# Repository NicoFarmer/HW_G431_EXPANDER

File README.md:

# HW_G431_EXPANDER
Carte électronique d'exention pour CPU STM32 G431KB

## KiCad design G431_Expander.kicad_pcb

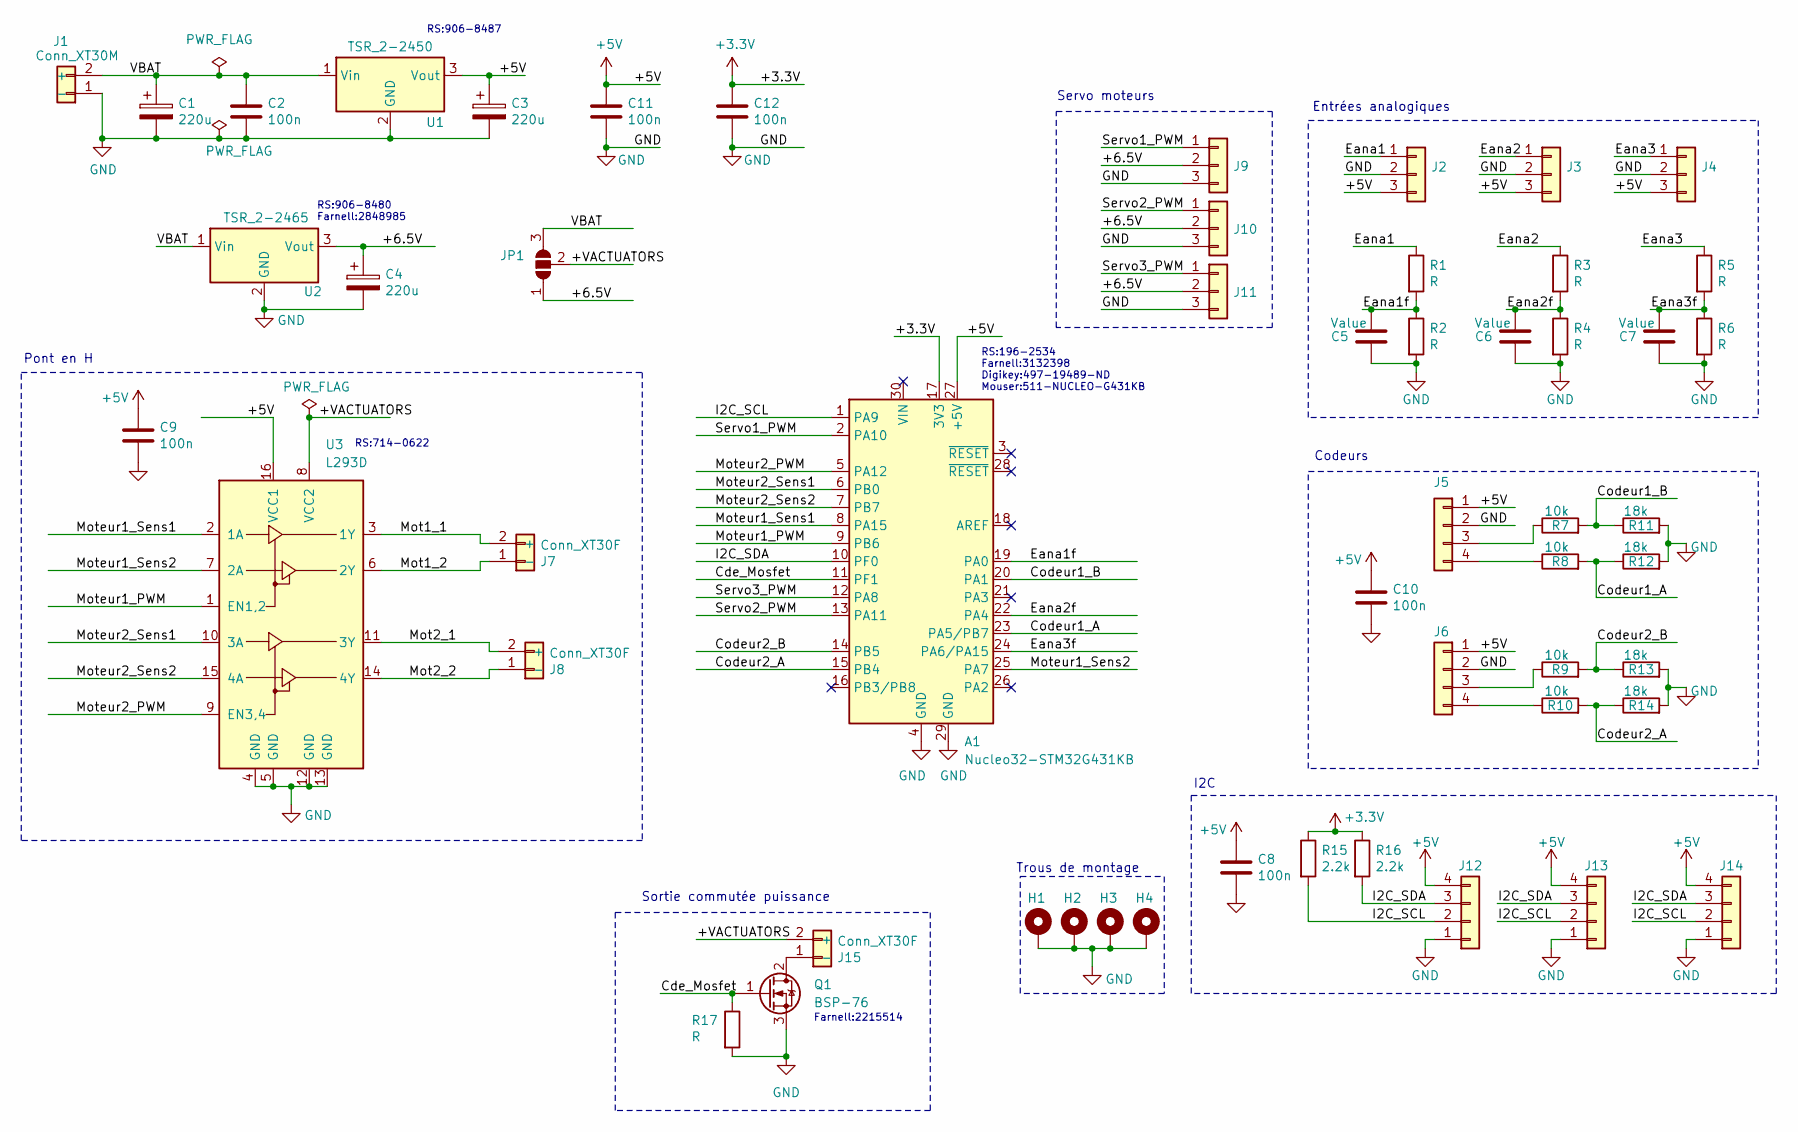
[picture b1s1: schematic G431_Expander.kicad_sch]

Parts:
A1: Nucleo32-STM32G431KB; Nucleo32-STM32-2x15pins
C1, C3, C4: 220u; C_Radial_D8.0mm_H11.5mm_P3.50mm
C2, C8, C9, C10, C11, C12: 100n; C_1206_3216Metric
C5, C6, C7: Value; C_1206_3216Metric
H1, H2, H3, H4: MountingHole_Pad; MountingHole_3.2mm_M3_Pad
J1: Conn_XT30M; AMASS_XT30UPB-M_1x02_P5.0mm_Vertical
J2, J3, J4: Conn_01x03; Molex_KK-254_AE-6410-03A_1x03_P2.54mm_Vertical
J5, J6, J12, J13, J14: Conn_01x04; Molex_KK-254_AE-6410-04A_1x04_P2.54mm_Vertical
J7, J8, J15: Conn_XT30F; AMASS_XT30UPB-F_1x02_P5.0mm_Vertical
J9, J10, J11: Conn_01x03; Servomotor-3x254
JP1: SolderJumper_3_Open; PinHeader_1x03_P2.54mm_Vertical
Q1: BSP-76; SOT-223-3_TabPin2
R1, R2, R3, R4, R5, R6, R17: R; R_1206_3216Metric
R7, R8, R9, R10: 10k; R_1206_3216Metric
R11, R12, R13, R14: 18k; R_1206_3216Metric
R15, R16: 2.2k; R_1206_3216Metric
U1: TSR_2-2450; Converter_DCDC_TRACO_TSR-1_THT
U2: TSR_2-2465; Converter_DCDC_TRACO_TSR-1_THT
U3: L293D; DIP-16_W7.62mm

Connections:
+3.3V: A1.17 (3V3), C12.1, R15.1, R16.1
+5V: A1.27 (+5V), C3.1, C8.1, C9.1, C10.1, C11.1, J2.3, J3.3, J4.3, J5.1, J6.1, J12.4, J13.4, J14.4, U1.3 (Vout), U3.16 (VCC1)
/+6.5V: C4.1, J9.2, J10.2, J11.2, JP1.1 (A), U2.3 (Vout)
/+VACTUATORS: J15.2 (+), JP1.2 (C), U3.8 (VCC2)
/Cde_Mosfet: A1.11 (PF1), Q1.1 (G), R17.1
/Codeur1_A: A1.23 (PA5/PB7), R8.2, R12.1
/Codeur1_B: A1.20 (PA1), R7.2, R11.1
/Codeur2_A: A1.15 (PB4), R10.2, R14.1
/Codeur2_B: A1.14 (PB5), R9.2, R13.1
/Eana1: J2.1, R1.1
/Eana1f: A1.19 (PA0), C5.2, R1.2, R2.1
/Eana2: J3.1, R3.1
/Eana2f: A1.22 (PA4), C6.2, R3.2, R4.1
/Eana3: J4.1, R5.1
/Eana3f: A1.24 (PA6/PA15), C7.2, R5.2, R6.1
/I2C_SCL: A1.1 (PA9), J12.2, J13.2, J14.2, R15.2
/I2C_SDA: A1.10 (PF0), J12.3, J13.3, J14.3, R16.2
/Mot1_1: J7.2 (+), U3.3 (1Y)
/Mot1_2: J7.1 (-), U3.6 (2Y)
/Mot2_1: J8.2 (+), U3.11 (3Y)
/Mot2_2: J8.1 (-), U3.14 (4Y)
/Moteur1_PWM: A1.9 (PB6), U3.1 (EN1,2)
/Moteur1_Sens1: A1.8 (PA15), U3.2 (1A)
/Moteur1_Sens2: A1.25 (PA7), U3.7 (2A)
/Moteur2_PWM: A1.5 (PA12), U3.9 (EN3,4)
/Moteur2_Sens1: A1.6 (PB0), U3.10 (3A)
/Moteur2_Sens2: A1.7 (PB7), U3.15 (4A)
/Servo1_PWM: A1.2 (PA10), J9.1
/Servo2_PWM: A1.13 (PA11), J10.1
/Servo3_PWM: A1.12 (PA8), J11.1
/VBAT: C1.1, C2.1, J1.2 (+), JP1.3 (B), U1.1 (Vin), U2.1 (Vin)
GND: A1.4 (GND), A1.29 (GND), C1.2, C2.2, C3.2, C4.2, C5.1, C6.1, C7.1, C8.2, C9.2, C10.2, C11.2, C12.2, H1.1, H2.1, H3.1, H4.1, J1.1 (-), J2.2, J3.2, J4.2, J5.2, J6.2, J9.3, J10.3, J11.3, J12.1, J13.1, J14.1, Q1.3 (S), R2.2, R4.2, R6.2, R11.2, R12.2, R13.2, R14.2, R17.2, U1.2 (GND), U2.2 (GND), U3.4 (GND), U3.5 (GND), U3.12 (GND), U3.13 (GND)
unnamed: J5.3, R7.1
unnamed: J5.4, R8.1
unnamed: J6.3, R9.1
unnamed: J6.4, R10.1
unnamed: J15.1 (-), Q1.2 (D)

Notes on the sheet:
RS:714-0622
Servo moteurs
Pont en H
I2C
Entrées analogiques
RS:196-2534 Farnell:3132398 Digikey:497-19489-ND Mouser:511-NUCLEO-G431KB
RS:906-8487
RS:906-8480 Farnell:2848985
Trous de montage
Codeurs
Farnell:2215514
Sortie commutée puissance

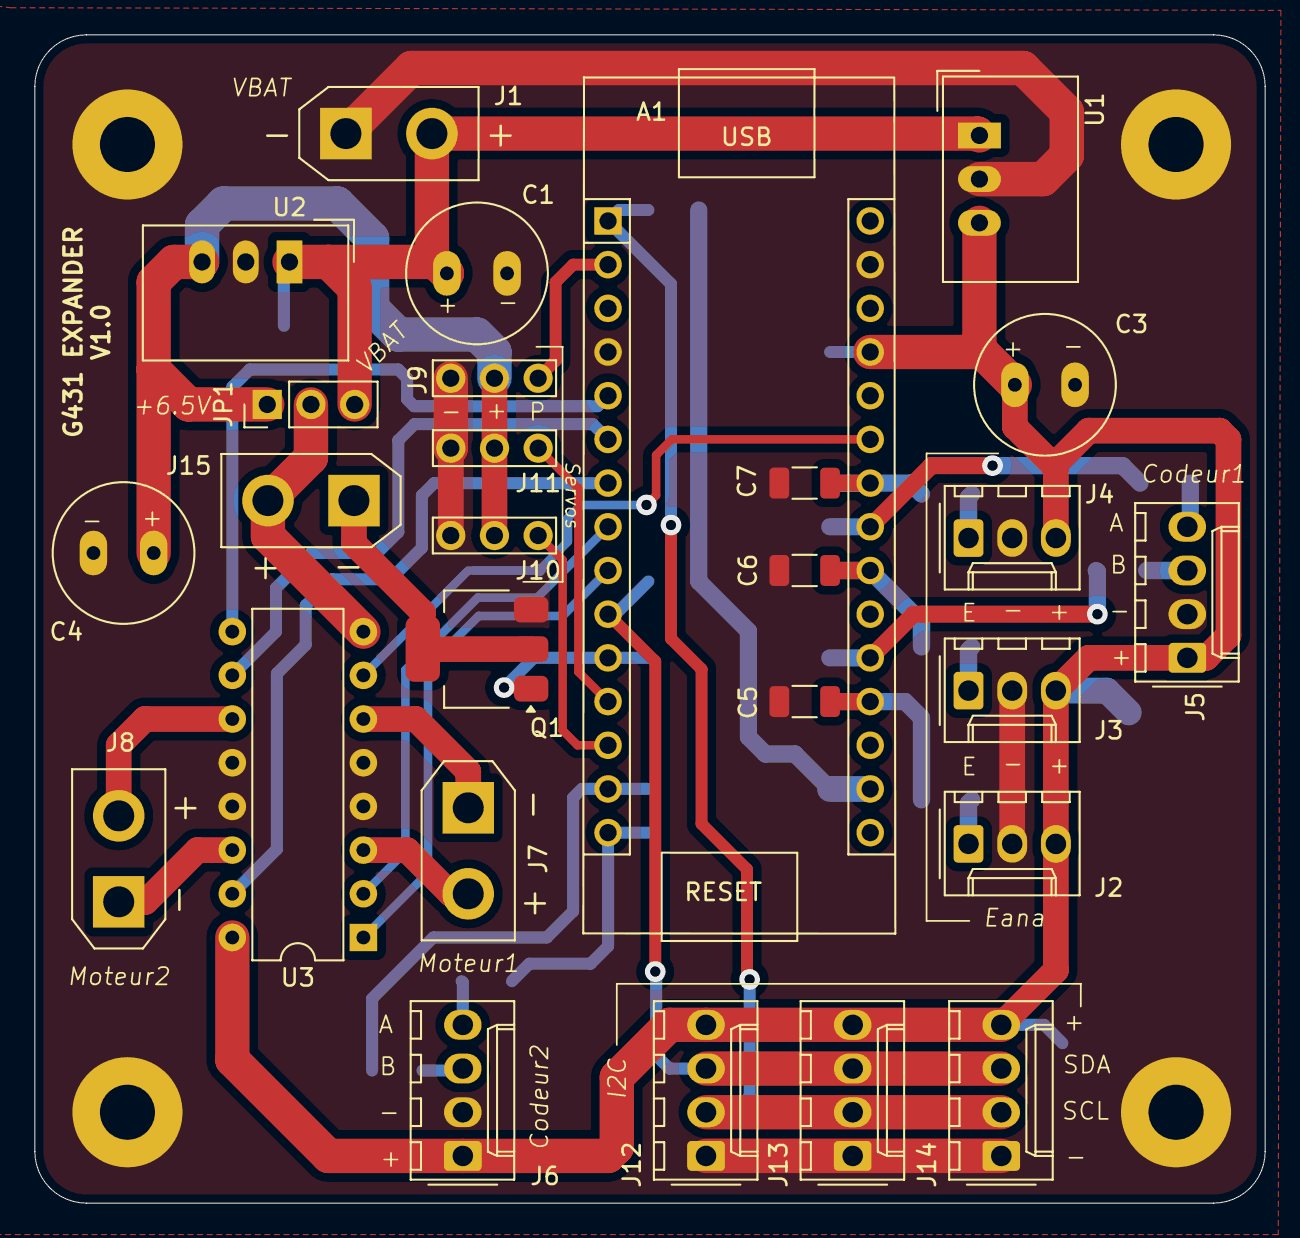
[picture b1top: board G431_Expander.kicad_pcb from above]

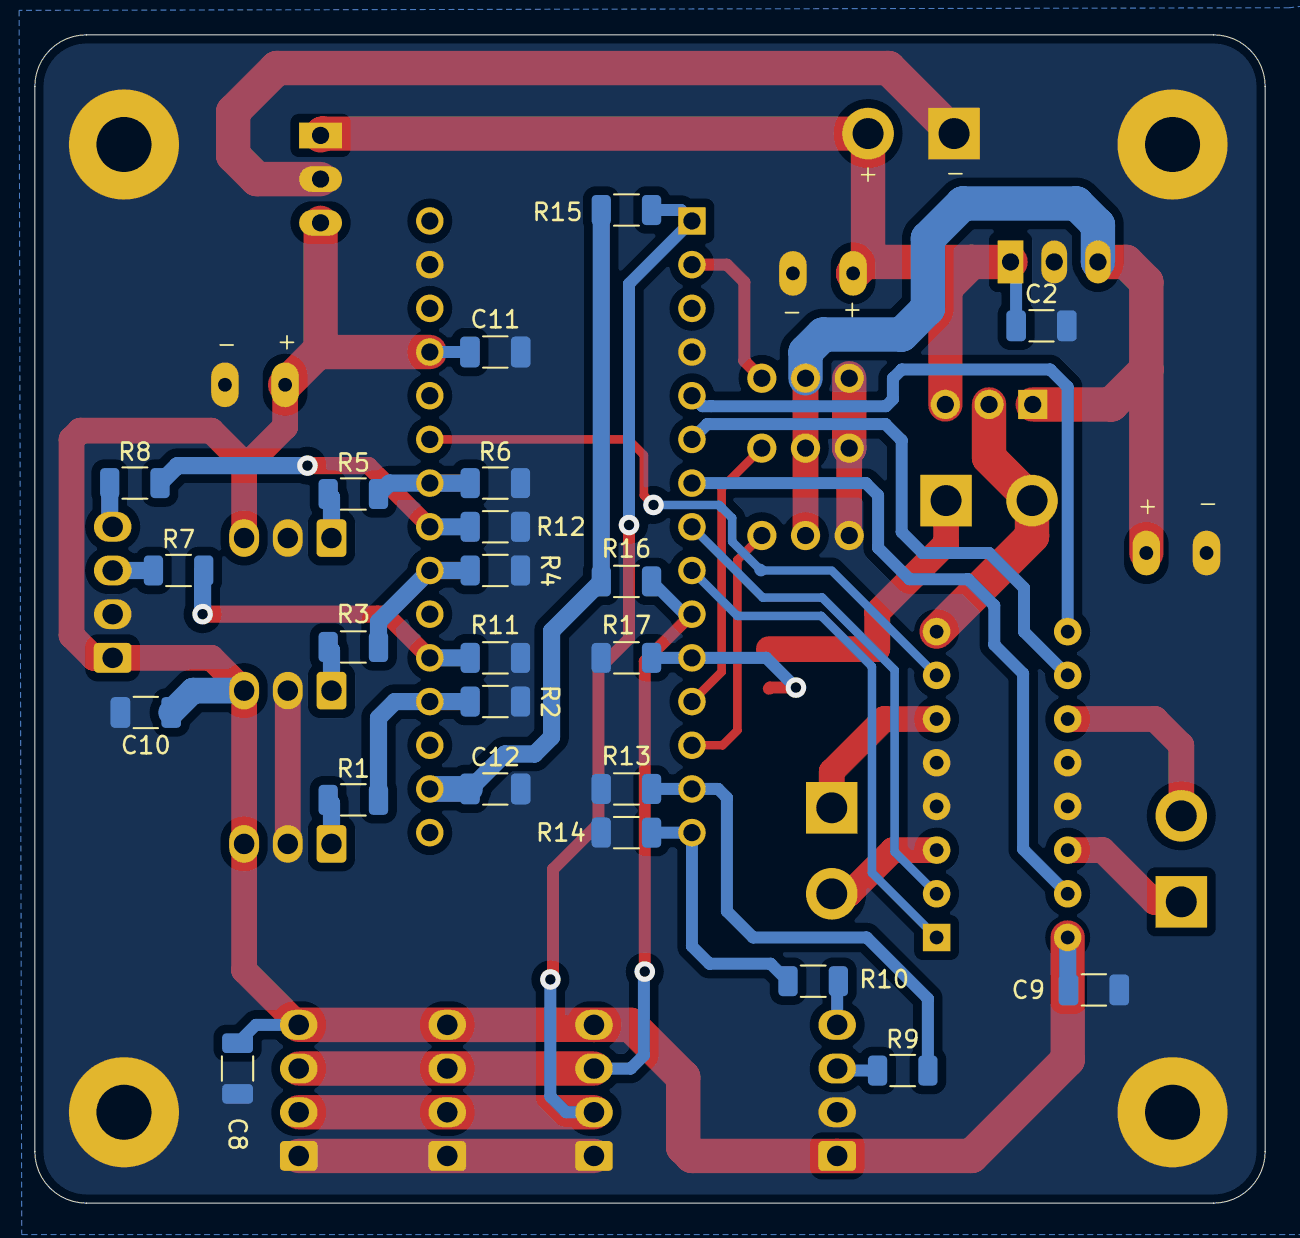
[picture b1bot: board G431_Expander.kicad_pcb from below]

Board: 2 copper layers, 71.5 x 67.9 mm, 54 parts (23 on the bottom side), 37 nets.

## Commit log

2025-01-26 Ajout du sous-module KICAD_LIB CRLG
2025-01-26 Ajout du fichier .gitignore
2025-01-26 Version initiale du schéma + routage
2025-01-26 Ajotu des fichiers gerber V1.0
